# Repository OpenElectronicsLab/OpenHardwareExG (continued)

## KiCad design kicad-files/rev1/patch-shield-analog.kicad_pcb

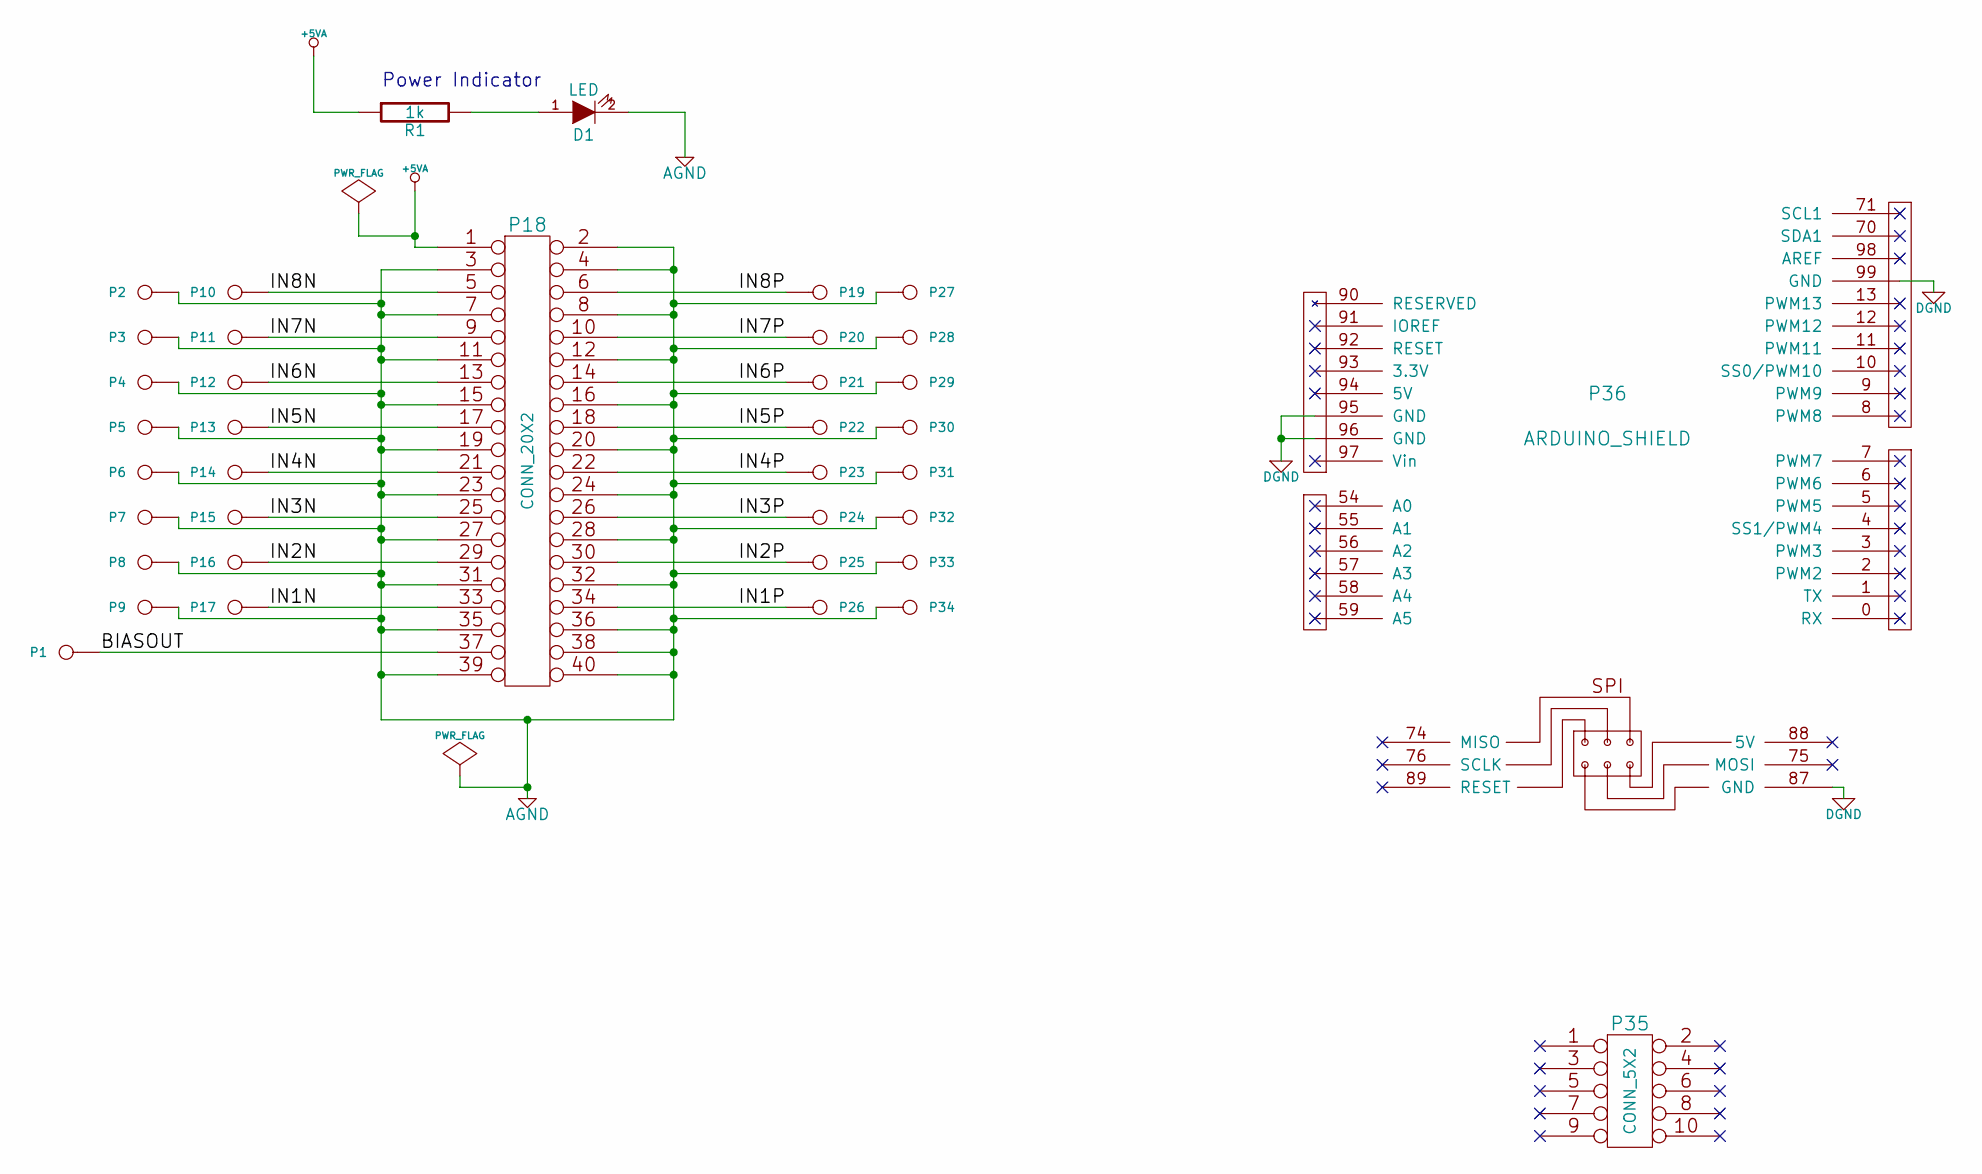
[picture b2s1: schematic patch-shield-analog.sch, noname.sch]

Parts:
D1: LED; SM0603
P1, P2, P3, P4, P5, P6, P7, P8, P9, P10, P11, P12, P13, P14, P15, P16, P17, P19, P20, P21, P22, P23, P24, P25, P26, P27, P28, P29, P30, P31, P32, P33, P34: CONN_1; Touchproof-socket
P18: CONN_20X2; PIN_ARRAY_20X2
P35: CONN_5X2; PIN_ARRAY_5x2
P36: ARDUINO_SHIELD; arduino_shield
R1: 1k; SM0603

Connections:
+5VA: P18.1, R1.1
/BIASOUT: P1.1, P18.37
/IN1N: P17.1, P18.33
/IN1P: P18.34, P26.1
/IN2N: P16.1, P18.29
/IN2P: P18.30, P25.1
/IN3N: P15.1, P18.25
/IN3P: P18.26, P24.1
/IN4N: P14.1, P18.21
/IN4P: P18.22, P23.1
/IN5N: P13.1, P18.17
/IN5P: P18.18, P22.1
/IN6N: P12.1, P18.13
/IN6P: P18.14, P21.1
/IN7N: P11.1, P18.9
/IN7P: P18.10, P20.1
/IN8N: P10.1, P18.5
/IN8P: P18.6, P19.1
AGND: D1.2 (K), P2.1, P3.1, P4.1, P5.1, P6.1, P7.1, P8.1, P9.1, P18.2, P18.3, P18.4, P18.7, P18.8, P18.11, P18.12, P18.15, P18.16, P18.19, P18.20, P18.23, P18.24, P18.27, P18.28, P18.31, P18.32, P18.35, P18.36, P18.38, P18.39, P18.40, P27.1, P28.1, P29.1, P30.1, P31.1, P32.1, P33.1, P34.1
DGND: P36.87 (GND), P36.95 (GND), P36.96 (GND), P36.99 (GND)
unnamed: D1.1 (A), R1.2

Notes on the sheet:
Power Indicator

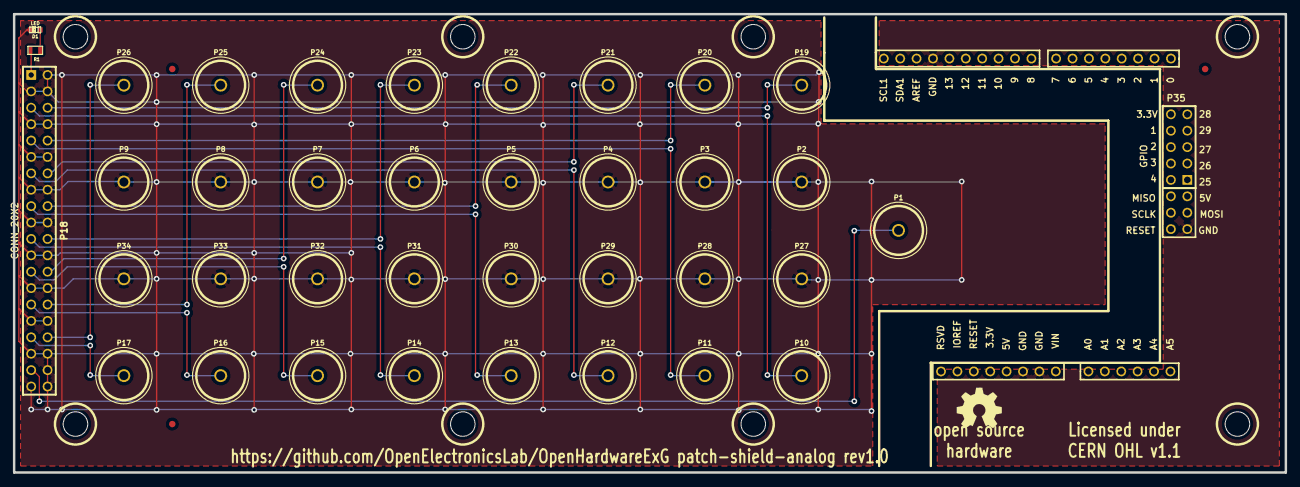
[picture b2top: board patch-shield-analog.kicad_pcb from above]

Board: 2 copper layers, 197.0 x 71.0 mm, 49 parts (0 on the bottom side), 21 nets.

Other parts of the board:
Hole_M3, Hole_M3#2, Hole_M3#3, Hole_M3#4, Hole_M3#5, Hole_M3#6, Hole_M3#7, Hole_M3#8: VAL**; Hole_M3
fiducial_mark: VAL**; fiducial_mark
fiducial_mark#2, fiducial_mark#3: VAL**; fiducial_mark

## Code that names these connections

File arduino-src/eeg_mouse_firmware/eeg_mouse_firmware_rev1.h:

/* eeg_mouse_firmware_rev1.h */
#ifndef _EEG_MOUSE_FIRMWARE_REV1_H_
#define _EEG_MOUSE_FIRMWARE_REV1_H_

// IPIN_ is for pins that are inverted

// CS (chip select) is PB14, CANTX1/IO, PIN53
#define IPIN_CS 53

//  SCLK (serial clock) is PA27, SPCK, SPI PIN 3
// #define PIN_SCLK

// DIN (data in) is  PA26, MOSI, SPI PIN 4
// #define PIN_DIN

// DOUT (data out) is PA25, MISO, SPI PIN 1
// #define PIN_DOUT

// CLKSEL (clock select) is PC14, PIN 49
#define PIN_CLKSEL 49

// RESET is PC15, PIN 48 (was PIN 47 in rev0)
#define IPIN_RESET 48

// PWDN (power down) is PC16, PIN 47 (was PIN 48 in rev0)
#define IPIN_PWDN 47

// START is PC17, PIN 46
#define PIN_START 46

// DRDY (data ready) is PC18, PIN 45
#define IPIN_DRDY 45

// LED_ENABLE is PD6, PIN 29
#define IPIN_LED_ENABLE 29

// LED_LATCH is PD3, PIN 28
#define PIN_LED_LATCH 28

// LED_CLEAR is PD2, PIN 27
#define IPIN_LED_CLEAR 27

// LED_CLK (LED clock) is PD1, PIN 26
#define PIN_LED_CLK 26

// LED_SERIAL is PD0, PIN 25
#define PIN_LED_SERIAL 25

#endif /* _EEG_MOUSE_FIRMWARE_REV_1_H_ */

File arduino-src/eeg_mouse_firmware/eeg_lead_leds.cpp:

#include <Arduino.h>
#include "eeg_mouse_firmware.h"
#include "eeg_lead_leds.h"

const int num_inputs_per_channel = 2;	// IN1N, IN1P
const int num_leds =
    Eeg_lead_leds::num_channels * num_inputs_per_channel * Eeg_lead_leds::num_colors;
const int states_per_led = 2;	// clock low and high

enum states {
	first_data_state = 0,
	last_data_state = (states_per_led * num_leds) - 1,
	latch_start,		// no value is the same as previous element + 1
	latch_end,
	last_state = latch_end
};

Eeg_lead_leds::Eeg_lead_leds()
{
	leds_state = 0;
	step = 0;
}

void Eeg_lead_leds::begin()
{
	// set up the pins for the LEDs
	pinMode(IPIN_LED_ENABLE, OUTPUT);
	pinMode(PIN_LED_LATCH, OUTPUT);
	pinMode(IPIN_LED_CLEAR, OUTPUT);
	pinMode(PIN_LED_CLK, OUTPUT);
	pinMode(PIN_LED_SERIAL, OUTPUT);

	digitalWrite(PIN_LED_LATCH, LOW);
	digitalWrite(PIN_LED_CLK, LOW);
	digitalWrite(IPIN_LED_ENABLE, LOW);

	// set LEDs to leds_state (probably 0, all off)
	update_all();
}

void Eeg_lead_leds::set_led(led_color color, int channel, polarity pol, bool on)
{
	int led_num = (num_colors * (channel + pol)) + color;
	uint32_t mask = (1 << led_num);

	leds_state = (leds_state & ~mask);
	if (on) {
		leds_state |= mask;
	}
}

void Eeg_lead_leds::set_green_positive(int channel, bool on)
{
	set_led(green, channel, positive, on);
}

void Eeg_lead_leds::set_yellow_positive(int channel, bool on)
{
	set_led(yellow, channel, positive, on);
}

void Eeg_lead_leds::set_green_negative(int channel, bool on)
{
	set_led(green, channel, negative, on);
}

void Eeg_lead_leds::set_yellow_negative(int channel, bool on)
{
	set_led(yellow, channel, negative, on);
}


void Eeg_lead_leds::update_tick()
{
	switch (step) {
	case latch_start:	// this happens almost last (defaults are first)
		// latch the data from the shift register to the LEDs
		digitalWrite(PIN_LED_LATCH, HIGH);
		++step;
		break;

	case latch_end:
		// reset the latch
		digitalWrite(PIN_LED_LATCH, LOW);
		step = 0;
		break;

	default:
		if (step % states_per_led == 0) {
			// ready the clock and set the data
			digitalWrite(PIN_LED_CLK, LOW);
			int bit_number_for_led = step / states_per_led;
			int bit_val = (1 & (leds_state >> bit_number_for_led));
			digitalWrite(PIN_LED_SERIAL, bit_val ? HIGH : LOW);
		} else {
			// clock out the data we set
			digitalWrite(PIN_LED_CLK, HIGH);
		}
		++step;
		break;
	}
}

void Eeg_lead_leds::update_all()
{
	step = 0;
	do {
		update_tick();
		delayMicroseconds(10);
	} while (step != 0);
}

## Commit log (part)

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2013-04-13 add ADuM4160 USB isolator to isolators.lib
2013-04-27 add capacitor valuesfor anti-aliasing filters
2013-05-05 add ferrite bead between USB shell and ground
2013-05-05 connect power to SAM3X
2013-05-05 connected USB to SAM3X
2013-05-12 powerdown unused channels on ads1298
    Chris Rorden suggested the practice of using PDn in conjunction with
    SHORTED to save power.
2013-05-18 added fuse and zener on isolated side
2013-05-18 added reset button
    A capacitor is not strictly required, but the data sheet
    recommends a 10nF capacitor in harsh environments.
    We chose a 100nF capacitor to keep the parts list and
    assembly instructions simple.
2013-05-18 added serial header for JY-MCU HC-06 bluetooth module
2013-05-18 connect ADS129x to SAM3X
2013-05-19 add yellow and green LEDs for each channel
2013-05-25 initial patch shield schematic
2013-05-25 move LEDs to patch-shield
2013-05-25 added power LED for patch shield
2013-05-26 Patch shield schematic cleanup
2013-05-27 Fix pin electrical type for SN74LVC1G3157
2013-06-01 Added buck regulator for 3.3V digital power
2013-06-01 replace 3.3v with buck regulator, add LC filter
2013-06-01 added the Si8663 isolator
2013-06-02 replace criss-crossed lines with labels
2013-06-02 add direction arrows to Si8663 symbol
2013-06-02 added Si8605 and Si8606 to isolator lib
2013-06-03 added digital isolators for ADS129x
2013-06-04 tidy power LED
2013-06-08 power Si86xx from 3.3V_ISO rather than super-quiet 3.3VADC
2013-06-08 create arduino-shield component
2013-06-08 add header for ADS129x_GPIO pins
2013-06-08 replace protection diodes on USB with USBLC6
2013-06-08 split patch-shield into analogue and digital boards
2013-06-09 add RS-485 and headers to bnc-shield
2013-06-09 fix wrongly labled pin
2013-06-09 fix floating labels
2013-06-09 fix more labels
2013-06-09 several little fixups with wires and labels
2013-06-09 more schematic fixups and tidy
2013-06-09 another floating label
2013-06-14 added zener diodes to provide some overvoltage protection
2013-06-14 Added 6V preregulator
2013-06-14 fix output pin type for 74AUP1G125GW
2013-06-15 fix pin types on SAM3X
2013-06-15 replace preregulator with crowbar circuits
2013-06-15 Labeled Ferrite Beads/INDUCTORs as MH2029-221Y
2013-06-15 improve port labels
2013-06-15 add netlist
2013-06-15 capacitors footprinted
2013-06-15 some headers footprinted
2013-06-16 diode footprint tweaks
2013-06-17 added footprint for 1.5 uH inductor
2013-06-18 added footprint for pushbutton
2013-06-19 added footprints for crystals
2013-06-21 added 64kB eeprom
2013-06-22 Fixed digital part of patch shield to pass ERC
2013-06-22 added I2C EEPROM to shields
2013-06-22 add reinforced isolation to power
2013-06-22 create a brd file
2013-06-22 starting analog patch shield layout
2013-06-22 locked more components
2013-06-24 added series resistors for noise reduction
2013-06-28 started schematic-based board layout
2013-06-29 fix inductor label rotation
2013-06-29 Fix addition inductor label rotations
2013-06-29 moved power to bottom margin
2013-06-29 grouped 3.3V switching reg. components
2013-06-29 fix pullup resistor for JTAG TMS
2013-07-01 Added alternative (linear) regulator for 3.3V
2013-07-05 routing around ads1299
2013-07-06 started routing around Si8662
2013-07-06 basic layout on board
2013-07-06 place touch-proof connectors on analog board
2013-07-06 connected right side of SI8662 isolator to SAM3X
2013-07-06 updated patch shield to new connector layout
2013-07-07 layout tracks in inner circle around SAM3X
2013-07-10 added mounting holes
2013-07-13 connect digital side of arduino shield headers
2013-07-13 swap order of lines through isolators to avoid as much crossing
2013-07-13 connect remaining I/O between ADS129x and SAM3X
2013-07-13 hooked up TPS7A4901 for isolated 5v and isolated 3v3
2013-07-13 make some of the power traces wider
2013-07-14 compact layout, wire up remaining signals on non-isolated side
2013-07-14 Removed remaining slots in ground plane by cleaning up A0-A5
2013-07-16 track cleanup and remaining ground planes
2013-07-18 added fiducial marks
2013-07-19 moved remaining labels to visibile positions
2013-07-20 add github url, board rev, improve labels
2013-07-20 clean up GPIO labels
2013-07-20 add reverse silk screen
2013-07-23 added pdf of schematic
2013-07-24 add pdf versions of the drill diagrams
2013-07-27 copy board outlines to patch shield
2013-07-27 resistors added to BOM
2013-07-27 few more parts on BOM
2013-07-29 add bnc connectors for digital signals
2013-08-02 add remaining part numbers to bom
2013-08-03 started BNC shield BOM
2013-08-03 import footprints
2013-08-03 make Rules Check pass
2013-08-03 add BoM for patch-shield-digital
2013-08-03 fix header of BoM
2013-08-03 fix paste error in LED partnum
2013-08-05 add unplated hole to touch-proof mounting footprint
2013-08-07 route analog patch-shield
2013-08-09 add digital status and activity LEDs to BNC board
2013-08-10 add Touchproof-socket-spacer for BiasOut
2013-08-10 initial LED traces on digital shield
2013-08-13 added initial brd file for bnc shield
2013-08-14 preliminary BNC shield connector layout
2013-08-17 move 74HC595 chips to right side of board
    this puts the fast changing digital signals further
    from the analog side of the board.
    also hopefull makes routing the traces a bit easier
2013-08-24 make text invisible
2013-08-24 hooked up 74HC595
2013-08-24 add grounding zones
2013-08-25 add text to patch-shield-analog
2013-08-25 nudge fiducial marks in from the edge
2013-08-25 make labels viewable on digital shield
2013-08-25 gerbers for patch-shield-analog
2013-11-09 replace narrow Si8606AC-B-IS1 with wider Si8606AD-B-IS to match footprint on board
2013-11-09 arduino-ads129x.brd : Fixed CAT24C128 footprint
2013-11-30 Added Arduino IDE compatible firmware for rev1
    The new eegmousefirmware directory contains a modified version of the code
    in arduino-src that can be used with the Arduino IDE to load the firmware
    onto a rev1 board.
    The Arduino IDE places several restrictions on file names: filenames can not
    contain dashes, the main file of a project must be named .ino (rather than
    .cpp), and the directory name must match the name of the main file.
2013-12-07 components for new filter settings
2013-12-15 make firmware sources compatable with Arduino IDE build
2013-12-15 Revert "Added Arduino IDE compatible firmware for rev1"
    This reverts commit dd7f65f1b69ed02d791ab0e5c61073cac01bbf87.
    Main project is now Arduino IDE compatible
2013-12-15 sketch out a start for dealing with different hardware versions
    Christoph Maier pointed out that PWDN and RESET were backwards,
    and indeed this highlights that rev0 and rev1 versions of our
    hardware have different pins for some purposes.
    More than just defines, currently have code which initializes
    the PINs 50, 15, and 52 which is important for rev0 and harmless
    for rev1. It would be better if we did not do confusing things.
2013-12-21 add ERASE button to schematic
2014-01-04 use -x to specify language for ino file
2014-01-11 Merge port reset from Christoph Maier
    removes the ruby dependency from the build
    (arguably increases linux dependency, but that is fine for now)
2014-01-18 add extra resolution (nV) to the signal chain
    We were seeing quantization of the data which turned out to be due to rounding of intermediate
    results to 6 decimal places when they were passed between scripts. We extended this to 9
    decimal places, which seems to have fixed the problems with quantization.
2014-01-19 add component numbers
2014-02-01 report chip ID from ADS129x during setup
2014-02-02 change to_hex to only need calling once
    -char to_hex(char byte, char high);
    +void to_hex(char byte, char *buf);
2014-02-09 turn on lead-off detection
2014-02-09 add delay for ads1299 power up
    It may take a bit longer for the power rails to stabilize on the isolated side of the
    board than it takes on the non-isolated side. This checkin adds a 300 ms delay before
    the SAM3X starts communicating with the ADS1299 to make sure the power has had time
    to stabilize.
2014-04-12 added IN1P t/m IN8N holes
2014-04-12 add screw holes
2014-04-12 add a bottom plank
2014-04-12 add comments to openscad file, whitespace tidy
2014-04-20 Expand screw holes to be proper size for #6 screws
    Our design had 3.6 mm screw holes that were a bit small for #6 screws,
    but Gold Phoenix PCB appears to have drilled larger 3.8 mm holes for our
    prototype boards (which is the size Machinery's Handbook recommends for
    a free clearance fit for this screw size). To save us from problems
    with future board runs, this check in expands the holes in the design to
    match the 3.8 mm size of the holes on the prototype boards.
2014-04-20 move origin to corner of pcb
2014-04-21 Visual tweaks: transparent case and dummy boards
    Add the boards as visual placeholders and make the case transparent.
    The transparency and color are only available in the OpenCSG renderer
    (i.e. when you press F5 rather than F6), but make it much easier to
    see how things fit together.
2014-04-22 Add nuts, hex holes, color cleanup
2014-04-25 Code cleanup: consolidate constants for dimensions
2014-04-26 Split the case OpenSCAD file into multiple files.
    It's useful to be able to render the case as both a 3D model and a 2D
    pattern that can be used with a laser cutter. It seems to be easiest to
    support this in OpenSCAD by using one file to render the 3D model
    (rev1_case_v1.scad) and a second file to render the 2D pattern
    (rev1_case_v1_pattern.scad). The code describing the case was left in
    the rev1_case_v1.scad file, as including the 3D model with the
2014-04-26 fix syntax error
2014-04-26 Fix horizontal header pin height, minor cleanups.
2014-04-26 shrink allowances a bit
2014-04-27 show how to round corners on a rectangle
2014-04-27 have plenty of Z margin when subtracting one solid from another
2014-05-01 Add front/back and a margin for slots to top/bottom
2014-05-02 Add slots for tabs
2014-05-03 give ourselves a little extra gap for easier assembly
2014-05-03 replace magic constant with descriptive name
2014-05-03 round out slot relief and reduce tab length
2014-05-03 s/ventilation/vent/g
2014-05-10 add link to gh-pages
2014-05-17 sketch an LED lighting object
2014-05-18 Add dependencies on header files
2014-05-18 Show leadoff LEDs whenever the device is on
2014-05-18 used only attached electrodes for bias reference
2014-05-31 add comment, formatting
2014-05-31 clarify code
2014-06-01 pattern for 2 cases on 1 Ponoko P2 sheet
2014-08-09 arduino-src/eeg_mouse_firmware -> OpenHardwareExG_firmware
2014-08-09 add gh-pages
2014-08-09 focus on the platfrom, not wires and such
2014-08-09 notes about electrode placement
2015-05-02 add supplier to bom-maker.pl
2015-12-05 add the *-cache.lib files for forward compatibility
2016-05-15 allow firmware for OpenHardwareExG_Shield
2016-05-15 added headers to tidy
    indent does not play super-nice with C++, sadly
2016-05-29 default GPIO to be the ADS1299 default
2016-06-12 add timestamp, print the git commit hash, fix reserved bits for CONFIG1
2020-07-04 copy gh-pages license explanation into README
2020-07-04 TODO look at OHL2 and submodules
2021-01-16 Update README, link schematic
2021-02-20 ignore kicad -bak files
2021-02-20 remove obsolete bnc shield
2021-02-20 remove obsolete rescue-backup
